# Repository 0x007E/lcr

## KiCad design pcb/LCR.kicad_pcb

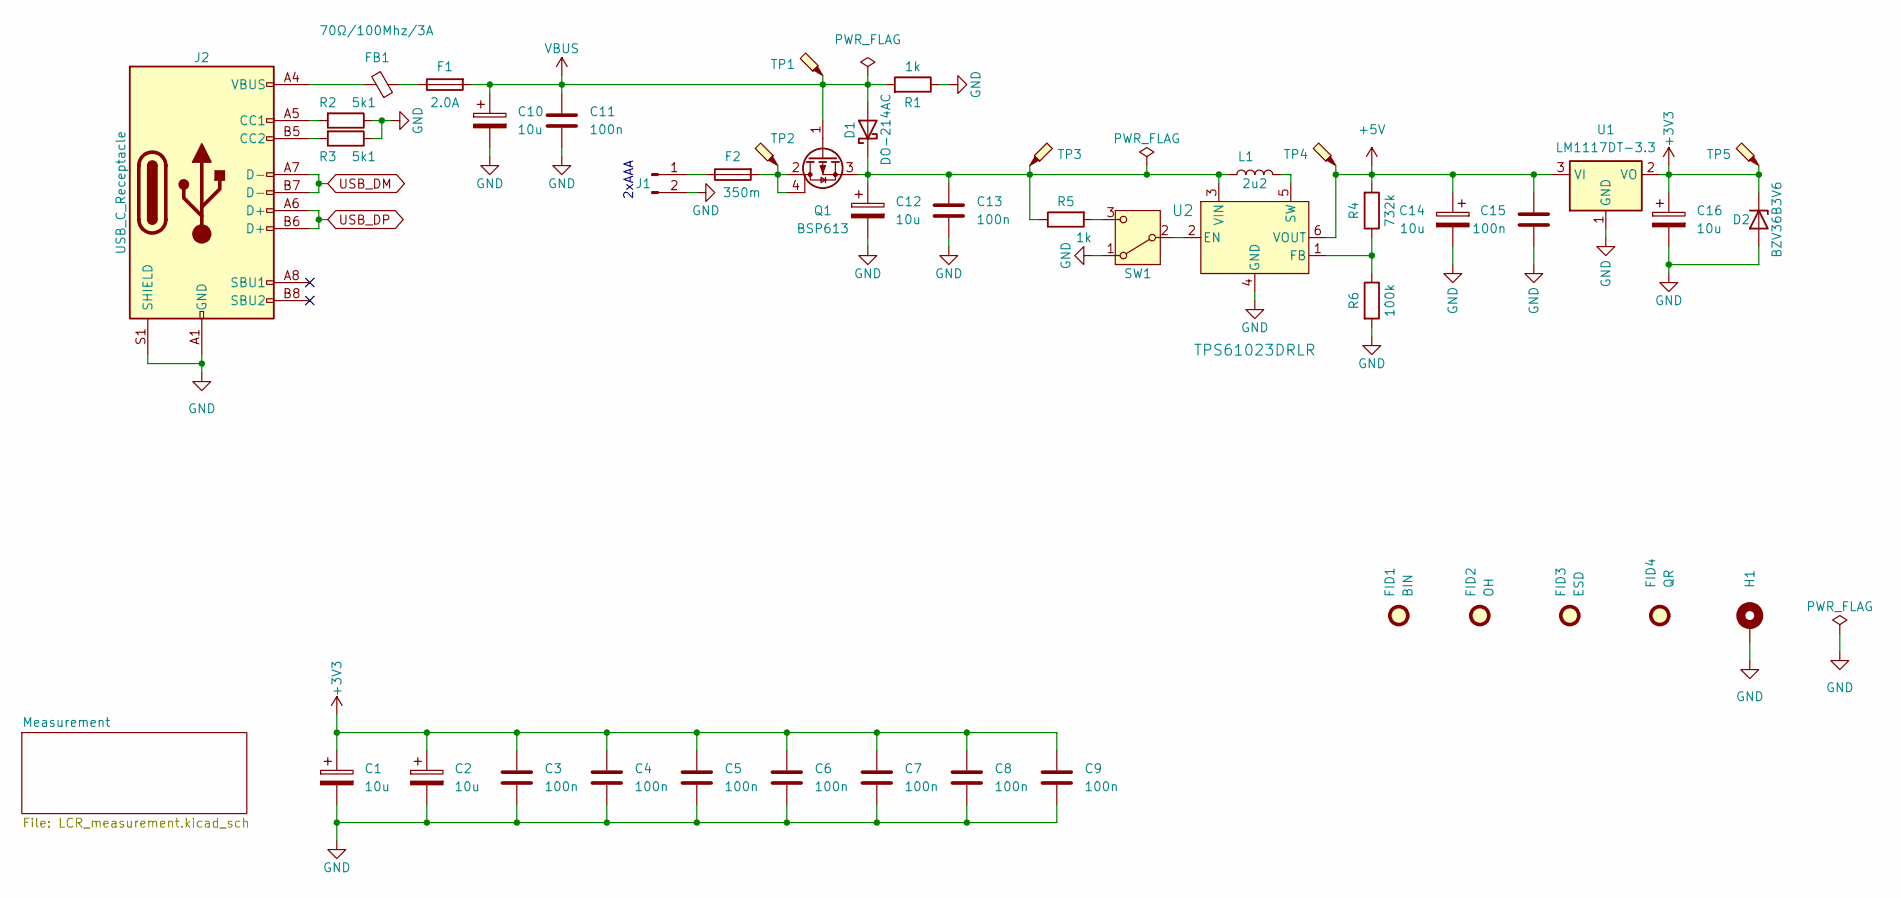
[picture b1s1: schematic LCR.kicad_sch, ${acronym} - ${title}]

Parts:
C1, C2, C10, C12, C14, C16: 10u; CP_EIA-3528-21_Kemet-B
C3, C4, C5, C6, C7, C8, C9, C11, C13, C15: 100n; C_1206_3216Metric
D1: DO-214AC; D_SMA
D2: BZV36B3V6; D_MiniMELF
F1: 2.0A; Fuse_1206_3216Metric
F2: 350m; Fuse_1206_3216Metric
FB1: 70Ω/100Mhz/3A; L_1206_3216Metric
FID1: BIN; WEEE-Logo_4.2x6mm_SilkScreen
FID2: OH; OSHW-Logo2_7.3x6mm_SilkScreen
FID3: ESD; ESD-Logo_6.6x6mm_SilkScreen
FID4: QR; QR_0x007e_very_small
H1: MountingHole_Pad; MountingHole_3.2mm_M3_DIN965_Pad
J1: Conn_01x02_Pin; JST_PH_S2B-PH-K_1x02_P2.00mm_Horizontal
J2: USB_C_Receptacle; USB_C_Receptacle_GCT_USB4110
L1: 2u2; L_Vishay_IFSC-1515AH_4x4x1.8mm
Q1: BSP613; SOT-223
R1, R5: 1k; R_1206_3216Metric
R2, R3: 5k1; R_1206_3216Metric
R4: 732k; R_1206_3216Metric
R6: 100k; R_1206_3216Metric
SW1: SW_SPDT; SW_SPDT_CK_JS102011SAQN
TP1, TP2, TP3, TP4, TP5: TestPoint_Probe; TestPoint_Pad_D1.0mm
U1: LM1117DT-3.3; TO-252-3_TabPin2
U2: TPS61023DRLR; SOT-563

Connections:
+3V3: C1.1, C2.1, C3.2, C4.2, C5.2, C6.2, C7.2, C8.2, C9.2, C16.1, D2.1 (K), TP5.1, U1.2 (VO); also elsewhere on the board
+5V: C14.1, C15.1, R4.2, TP4.1, U1.3 (VI), U2.6 (VOUT)
GND: C1.2, C2.2, C3.1, C4.1, C5.1, C6.1, C7.1, C8.1, C9.1, C10.2, C11.2, C12.2, C13.2, C14.2, C15.2, C16.2, D2.2 (A), H1.1, J1.2, J2.A1 (GND), J2.A12 (GND), J2.B1 (GND), J2.B12 (GND), J2.S1 (SHIELD), R1.1, R2.1, R3.1, R6.2, SW1.1 (A), U1.1 (GND), U2.4 (GND); also elsewhere on the board
unnamed: C12.1, C13.1, D1.1 (K), L1.1, Q1.3 (S), R5.1, TP3.1, U2.3 (VIN)
unnamed: F1.1, FB1.1
unnamed: F2.2, Q1.2 (D), Q1.4 (D), TP2.1
unnamed: FB1.2, J2.A4 (VBUS), J2.A9 (VBUS), J2.B4 (VBUS), J2.B9 (VBUS)
unnamed: F2.1, J1.1
unnamed: J2.A5 (CC1), R2.2
unnamed: J2.B5 (CC2), R3.2
unnamed: SW1.2 (B), U2.2 (EN)
unnamed: R5.2, SW1.3 (C)
unnamed: R4.1, R6.1, U2.1 (FB)
unnamed: L1.2, U2.5 (SW)
USB_DM: J2.A7 (D-), J2.B7 (D-); also elsewhere on the board
USB_DP: J2.A6 (D+), J2.B6 (D+); also elsewhere on the board
VBUS: C10.1, C11.1, D1.2 (A), F1.2, Q1.1 (G), R1.2, TP1.1; also elsewhere on the board

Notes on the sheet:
2xAAA

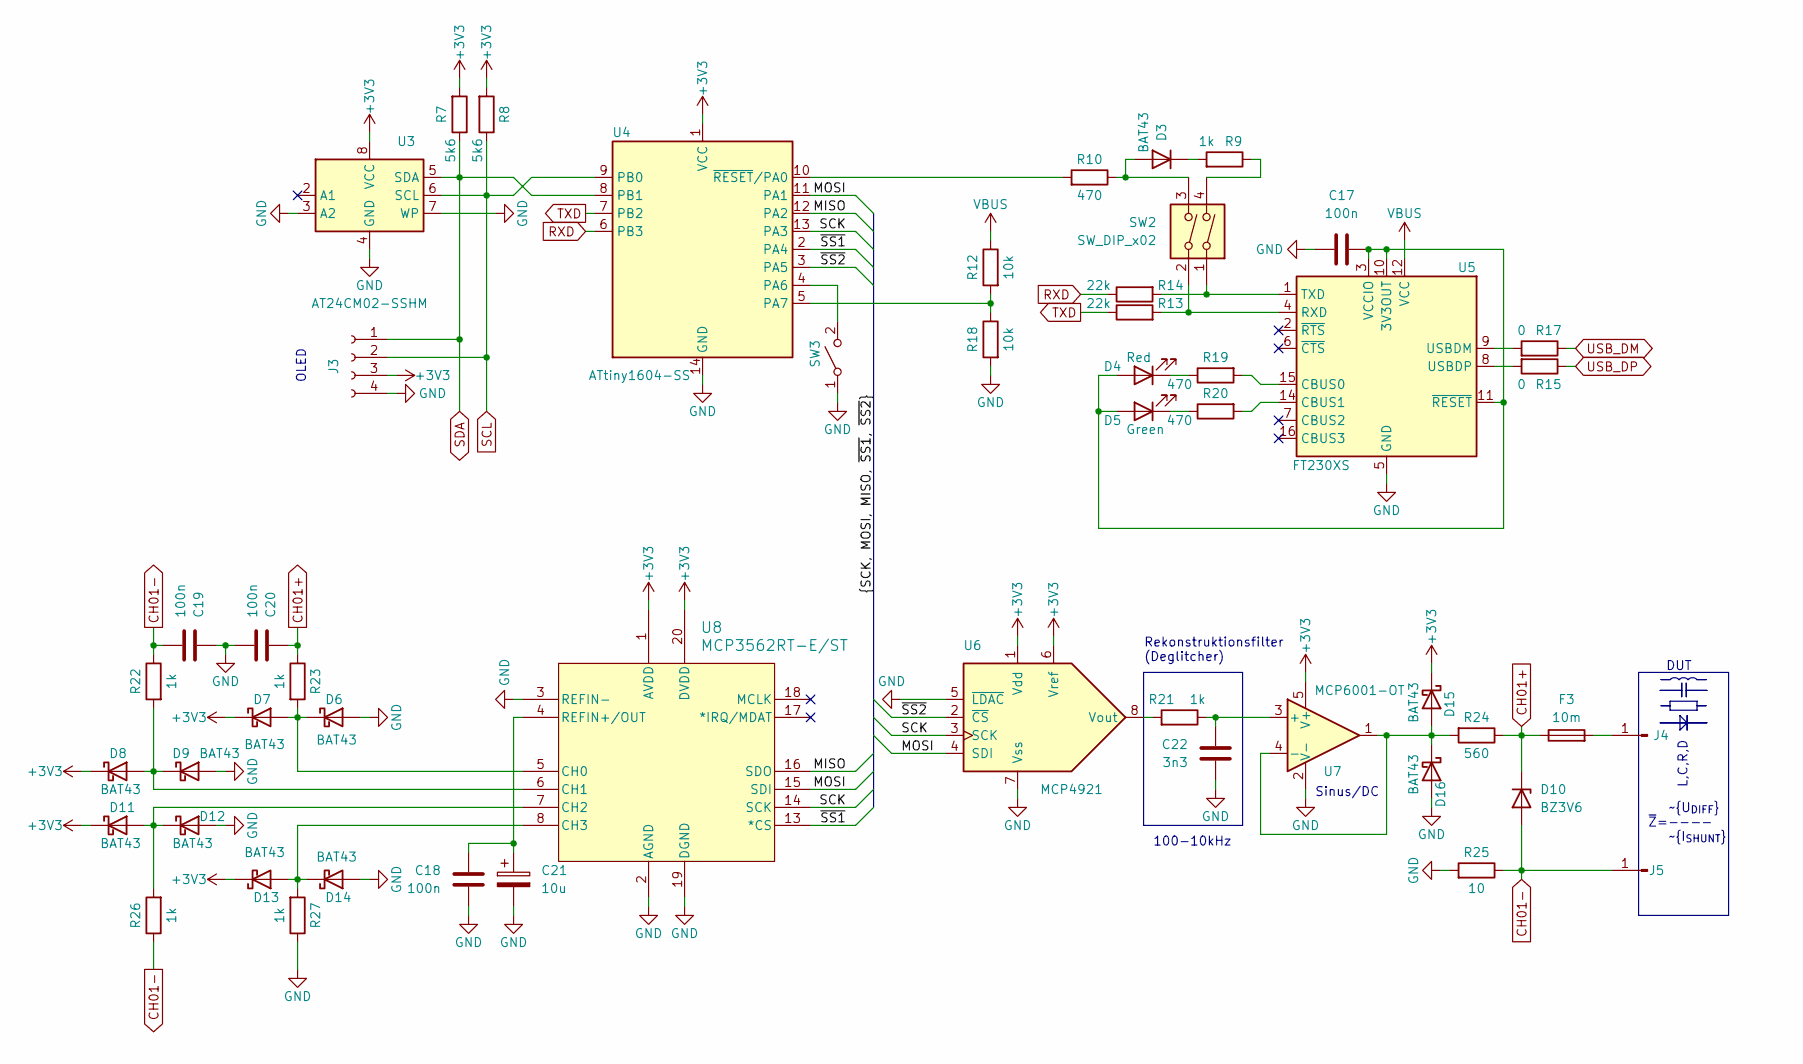
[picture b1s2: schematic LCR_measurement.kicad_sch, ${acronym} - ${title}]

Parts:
C17, C18, C19, C20: 100n; C_1206_3216Metric
C21: 10u; CP_EIA-3528-21_Kemet-B
C22: 3n3; C_1206_3216Metric
D3, D6, D7, D8, D9, D11, D12, D13, D14, D15, D16: BAT43; D_MiniMELF
D4: Red; LED_1206_3216Metric
D5: Green; LED_1206_3216Metric
D10: BZ3V6; D_MiniMELF
F3: 10m; Fuse_0603_1608Metric; DigiKey 18-0603L001/60YRCT-ND
J3: Conn_01x04_Socket; PinSocket_1x04_P2.54mm_Vertical
J4, J5: Conn_01x01_Pin; SolderWire-0.25sqmm_1x01_D0.65mm_OD2mm
R7, R8: 5k6; R_1206_3216Metric
R9, R21, R22, R23, R26, R27: 1k; R_1206_3216Metric
R10, R19, R20: 470; R_1206_3216Metric
R12, R18: 10k; R_1206_3216Metric
R13, R14: 22k; R_1206_3216Metric
R15, R17: 0; R_0603_1608Metric; DigiKey RMCF0603ZT0R00CT-ND
R24: 560; R_1206_3216Metric
R25: 10; R_1206_3216Metric
SW2: SW_DIP_x02; SW_DIP_SPSTx02_Slide_6.7x6.64mm_W8.61mm_P2.54mm_LowProfile
SW3: SW_SPST; SW_SPST_PTS645
U3: AT24CM02-SSHM; SOIC-8_3.9x4.9mm_P1.27mm
U4: ATtiny1604-SS; SOIC-14_3.9x8.7mm_P1.27mm
U5: FT230XS; SSOP-16_3.9x4.9mm_P0.635mm
U6: MCP4921; SOIC-8_3.9x4.9mm_P1.27mm; DigiKey MCP4921T-E/SNCT-ND
U7: MCP6001-OT; SOT-23-5; DigiKey MCP6001T-I/OTCT-ND
U8: MCP3562RT-E/ST; TSSOP-20_4.4x6.5mm_P0.65mm; DigiKey 150-MCP3562RT-E/STCT-ND

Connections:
+3V3: D7.1 (K), D8.1 (K), D11.1 (K), D13.1 (K), D15.1 (K), J3.3, R7.2, R8.2, U3.8 (VCC), U4.1 (VCC), U6.1 (Vdd), U6.6 (Vref), U7.5 (V+), U8.1 (AVDD), U8.20 (DVDD); also elsewhere on the board
/Measurement/MISO: U4.12 (PA2), U8.16 (SDO)
/Measurement/MOSI: U4.11 (PA1), U6.4 (SDI), U8.15 (SDI)
/Measurement/SCK: U4.13 (PA3), U6.3 (SCK), U8.14 (SCK)
/Measurement/~SS1: U4.2 (PA4), U8.13 (*CS)
/Measurement/~SS2: U4.3 (PA5), U6.2 (~CS)
CH01+: C20.2, D10.1 (K), F3.1, R23.1, R24.1
CH01-: C19.1, D10.2 (A), J5.1, R22.1, R25.1, R26.1
GND: C17.2, C18.2, C19.2, C20.1, C21.2, C22.2, D6.2 (A), D9.2 (A), D12.2 (A), D14.2 (A), D16.2 (A), J3.4, R18.2, R25.2, R27.1, SW3.1 (A), U3.3 (A2), U3.4 (GND), U3.7 (WP), U4.14 (GND), U5.5 (GND), U5.13 (GND), U6.5 (~LDAC), U6.7 (Vss), U7.2 (V-), U8.2 (AGND), U8.3 (REFIN-), U8.19 (DGND); also elsewhere on the board
unnamed: D3.2 (A), R10.1, SW2.3
unnamed: D3.1 (K), R9.2
unnamed: C17.1, D4.2 (A), D5.2 (A), U5.3 (VCCIO), U5.10 (3V3OUT), U5.11 (~RESET)
unnamed: D4.1 (K), R19.1
unnamed: D5.1 (K), R20.1
unnamed: D6.1 (K), D7.2 (A), R23.2, U8.5 (CH0)
unnamed: D8.2 (A), D9.1 (K), R22.2, U8.6 (CH1)
unnamed: D11.2 (A), D12.1 (K), R26.2, U8.7 (CH2)
unnamed: D13.2 (A), D14.1 (K), R27.2, U8.8 (CH3)
unnamed: D15.2 (A), D16.1 (K), R24.2, U7.1, U7.4 (-)
unnamed: F3.2, J4.1
unnamed: R9.1, SW2.4
unnamed: SW3.2 (B), U4.4 (PA6)
unnamed: R12.2, R18.1, U4.5 (PA7)
unnamed: R10.2, U4.10 (~RESET/PA0)
unnamed: R19.2, U5.15 (CBUS0)
unnamed: R20.2, U5.14 (CBUS1)
unnamed: R13.2, SW2.2, U5.4 (RXD)
unnamed: R14.2, SW2.1, U5.1 (TXD)
unnamed: R17.2, U5.9 (USBDM)
unnamed: R15.2, U5.8 (USBDP)
unnamed: R21.2, U6.8 (Vout)
unnamed: C22.1, R21.1, U7.3 (+)
unnamed: C18.1, C21.1, U8.4 (REFIN+/OUT)
RXD: R14.1, U4.6 (PB3)
SCL: J3.2, R8.1, U3.6 (SCL), U4.9 (PB0)
SDA: J3.1, R7.1, U3.5 (SDA), U4.8 (PB1)
TXD: R13.1, U4.7 (PB2)
USB_DM: R17.1; also elsewhere on the board
USB_DP: R15.1; also elsewhere on the board
VBUS: R12.1, U5.12 (VCC); also elsewhere on the board

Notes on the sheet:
OLED
100-10kHz
Sinus/DC
DUT
Rekonstruktionsfilter (Deglitcher)
~{U_{DIFF}} ~{Z}=---- ~{I_{SHUNT}}
L,C,R,D

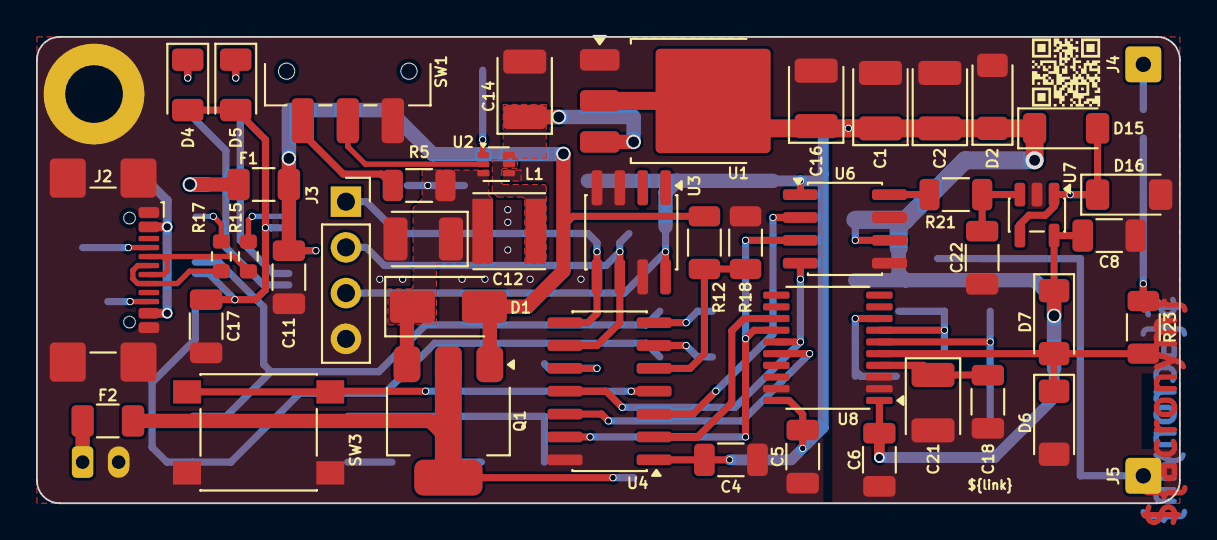
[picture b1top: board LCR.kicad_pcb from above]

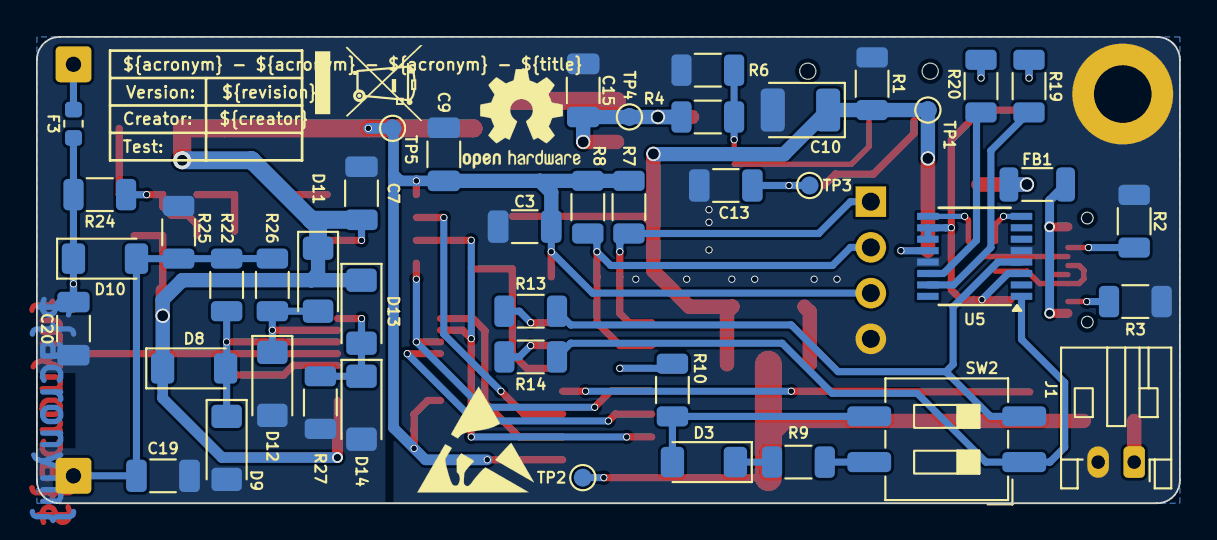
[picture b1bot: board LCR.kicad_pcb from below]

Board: 2 copper layers, 63.5 x 25.9 mm, 95 parts (47 on the bottom side), 52 nets.

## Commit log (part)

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2026-05-22 Add pcb layout
2026-05-22 Set grid reference
2026-05-22 Add/fix missing/wrong vendor(id)
2026-06-04 Change MCP2221A to FT230X
2026-06-04 Rename/Add/Remove bom fields

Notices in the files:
parts and their libraries:
license: CC BY-NC-SA 4.0
